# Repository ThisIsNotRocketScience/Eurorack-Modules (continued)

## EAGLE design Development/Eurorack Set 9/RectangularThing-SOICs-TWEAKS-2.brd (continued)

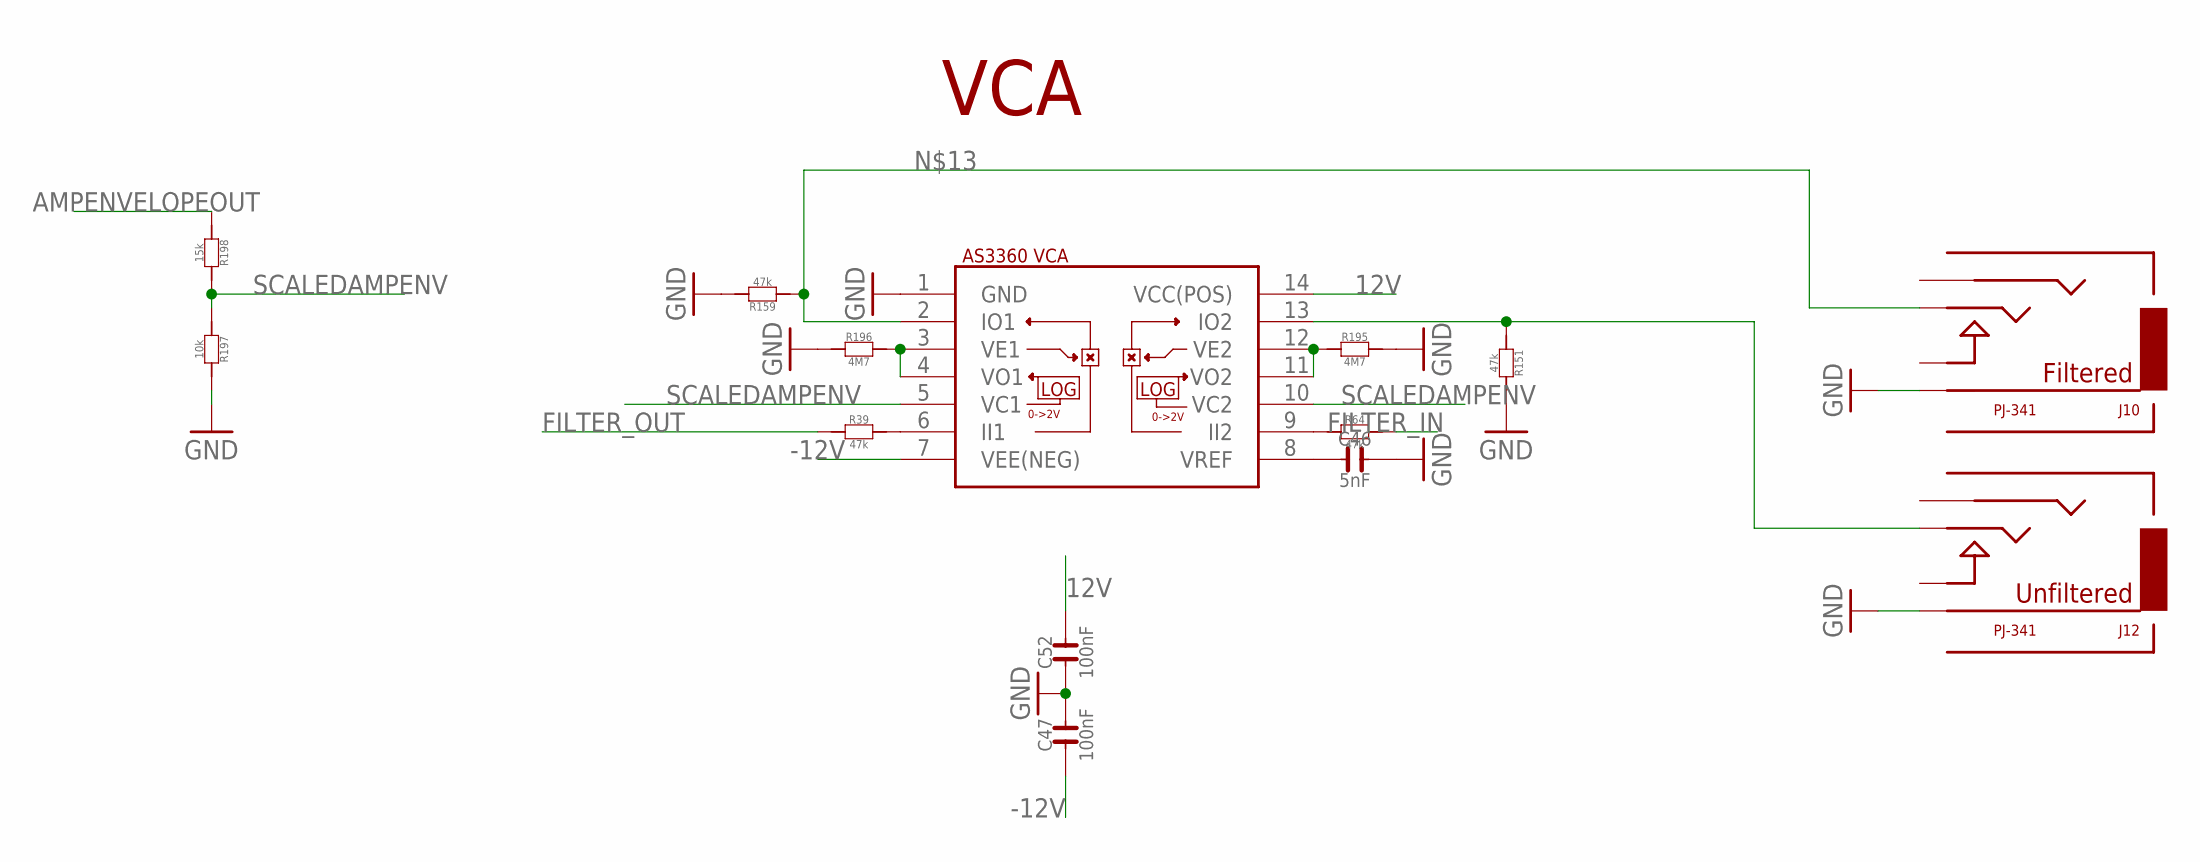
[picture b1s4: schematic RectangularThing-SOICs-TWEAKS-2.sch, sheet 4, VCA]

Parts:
C46: 5nF; C0603
C47, C52: 100nF; C0603
IC14: CEM3360SOIC14; SO14
J10, J12: PJ-341; 3.5MM-JACK-SWITCH-13MM-OUTPUT
R39, R64, R151, R159: 47k; R0603
R195, R196: 4M7; R0603
R197: 10k; R0603
R198: 15k; R0603

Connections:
12V: C52.2, IC14.14 (VCC(POS)); also elsewhere on the board
-12V: C47.1, IC14.7 (VEE(NEG)); also elsewhere on the board
AMPENVELOPEOUT: R198.1; also elsewhere on the board
FILTER_IN: R64.2; also elsewhere on the board
FILTER_OUT: R39.1; also elsewhere on the board
GND: C46.2, C47.2, C52.1, IC14.1 (GND), J10.RING@3 (RING), J12.RING@3 (RING), R151.2, R159.2, R195.2, R196.1, R197.2; also elsewhere on the board
unnamed: C46.1, IC14.8 (VREF)
unnamed: IC14.3 (VE1), IC14.4 (VO1), R196.2
unnamed: IC14.2 (IO1), J10.TIP@3 (TIP), R159.1
unnamed: IC14.13 (IO2), J12.TIP@3 (TIP), R151.1
unnamed: IC14.11 (VO2), IC14.12 (VE2), R195.1
unnamed: IC14.9 (II2), R64.1
unnamed: IC14.6 (II1), R39.2
SCALEDAMPENV: IC14.5 (VC1), IC14.10 (VC2), R197.1, R198.2

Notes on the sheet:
VCA

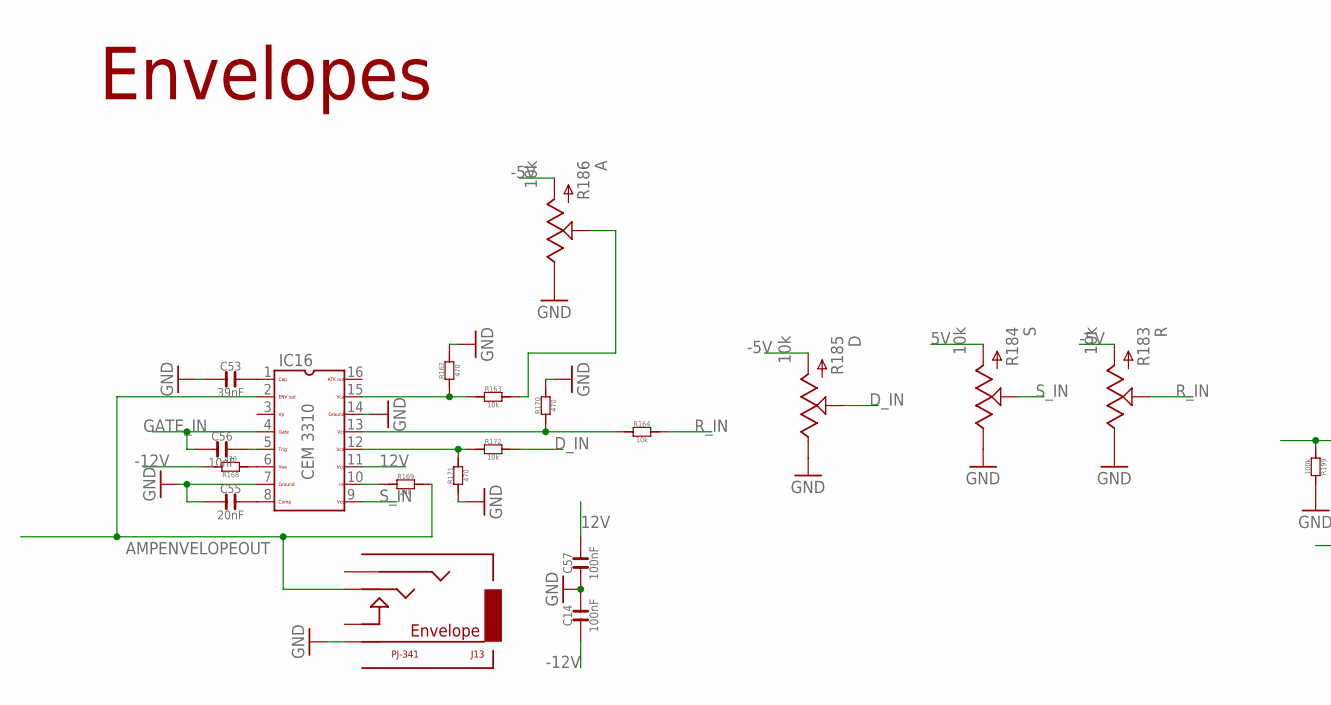
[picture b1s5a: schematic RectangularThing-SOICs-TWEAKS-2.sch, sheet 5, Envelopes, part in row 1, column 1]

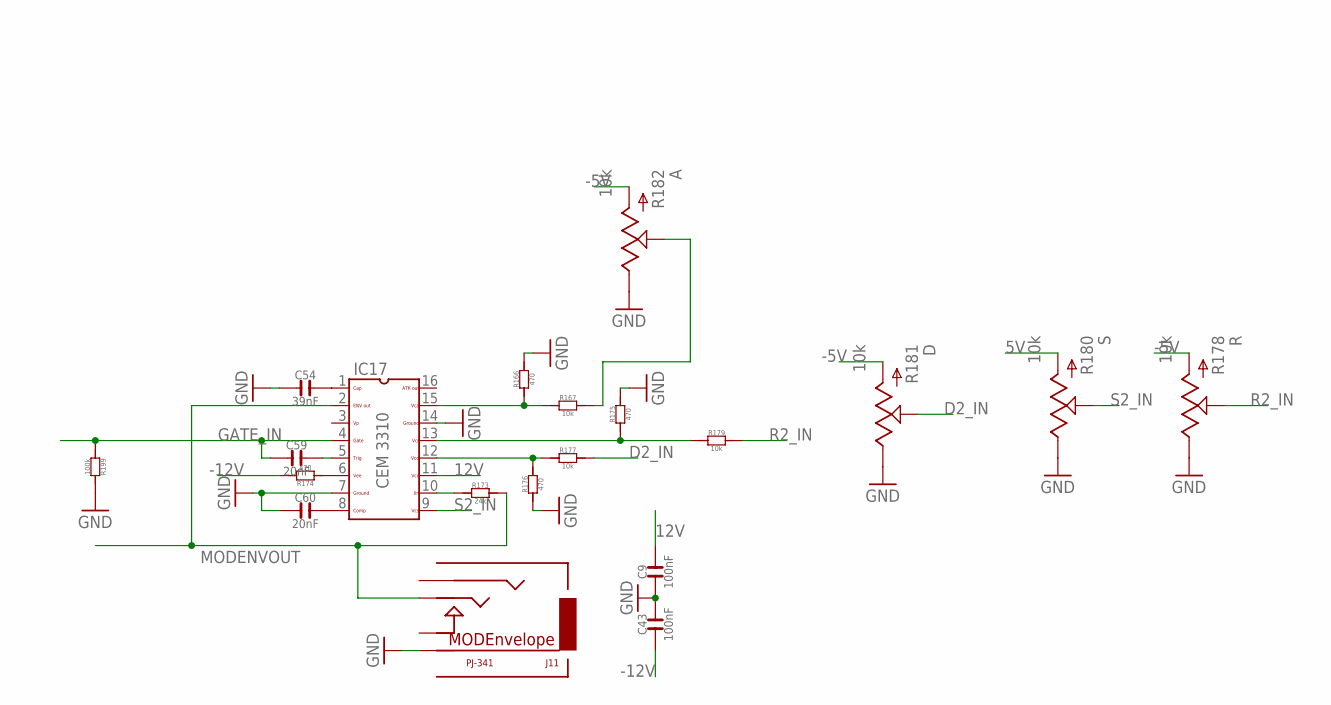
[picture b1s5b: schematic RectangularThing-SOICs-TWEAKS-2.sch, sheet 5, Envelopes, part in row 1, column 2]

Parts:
C9, C14, C43, C57: 100nF; C0603
C53, C54: 39nF; C0603
C55, C59, C60: 20nF; C0603
C56: 10nF; C0603
IC16, IC17: CEM3310SOIC16; SO16
J11, J13: PJ-341; 3.5MM-JACK-SWITCH-13MM-OUTPUT
R162, R166, R168, R170, R171, R174, R175, R176: 470; R0603
R163, R164, R167, R172, R177, R179: 10k; R0603
R169, R173: 24k; R0603
R178, R180, R181, R182, R183, R184, R185, R186: 10k; OG-POTS_ALPS_POT_VERTICAL
R199: 100k; R0603

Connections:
5V: R180.P$3 (A), R184.P$3 (A); also elsewhere on the board
12V: C9.2, C57.2, IC16.11, IC17.11; also elsewhere on the board
-5V: R178.P$3 (A), R181.P$3 (A), R182.P$3 (A), R183.P$3 (A), R185.P$3 (A), R186.P$3 (A); also elsewhere on the board
-12V: C14.1, C43.1, R168.2, R174.2; also elsewhere on the board
A2_IN: R167.2, R182.P$2 (S)
AMPENVELOPEOUT: IC16.2, J13.TIP@3 (TIP), R169.2; also elsewhere on the board
A_IN: R163.2, R186.P$2 (S)
D2_IN: R177.2, R181.P$2 (S)
D_IN: R172.2, R185.P$2 (S)
GATE_IN: C56.1, C59.1, IC16.4, IC17.4, R199.1; also elsewhere on the board
GND: C9.1, C14.2, C43.2, C53.1, C54.1, C55.1, C57.1, C60.1, IC16.7, IC16.14, IC17.7, IC17.14, J11.RING@3 (RING), J13.RING@3 (RING), R162.2, R166.2, R170.2, R171.1, R175.2, R176.1, R178.P$1 (E), R180.P$1 (E), R181.P$1 (E), R182.P$1 (E), R183.P$1 (E), R184.P$1 (E), R185.P$1 (E), R186.P$1 (E), R199.2; also elsewhere on the board
MODENVOUT: IC17.2, J11.TIP@3 (TIP), R173.2; also elsewhere on the board
unnamed: IC16.15, R162.1, R163.1
unnamed: IC16.12, R171.2, R172.1
unnamed: IC16.13, R164.1, R170.1
unnamed: C53.2, IC16.1
unnamed: C56.2, IC16.5
unnamed: IC16.6, R168.1
unnamed: C55.2, IC16.8
unnamed: IC16.10, R169.1
unnamed: IC17.15, R166.1, R167.1
unnamed: IC17.12, R176.2, R177.1
unnamed: IC17.13, R175.1, R179.1
unnamed: C59.2, IC17.5
unnamed: IC17.6, R174.1
unnamed: C60.2, IC17.8
unnamed: IC17.10, R173.1
unnamed: C54.2, IC17.1
R2_IN: R178.P$2 (S), R179.2
R_IN: R164.2, R183.P$2 (S)
S2_IN: IC17.9, R180.P$2 (S)
S_IN: IC16.9, R184.P$2 (S)

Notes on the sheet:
Envelopes

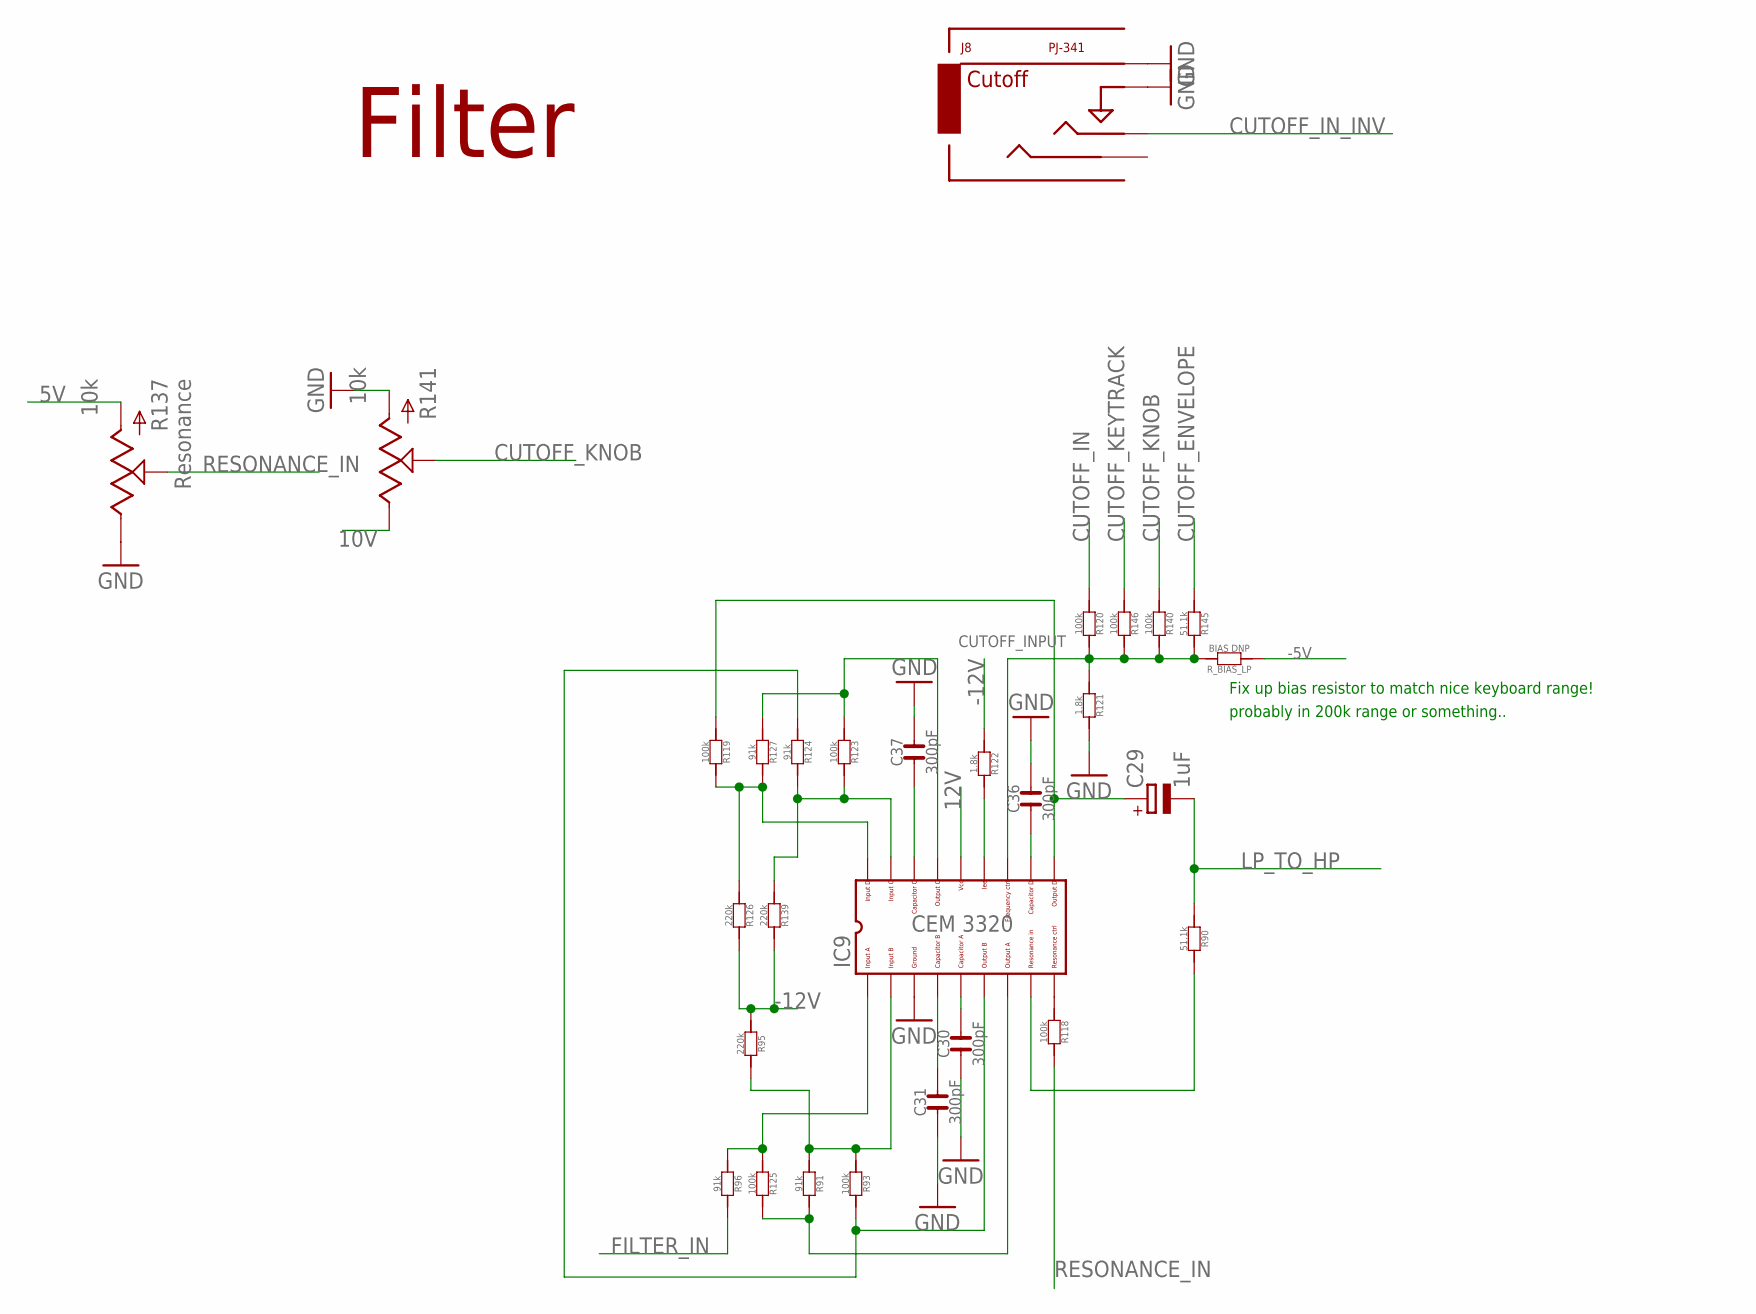
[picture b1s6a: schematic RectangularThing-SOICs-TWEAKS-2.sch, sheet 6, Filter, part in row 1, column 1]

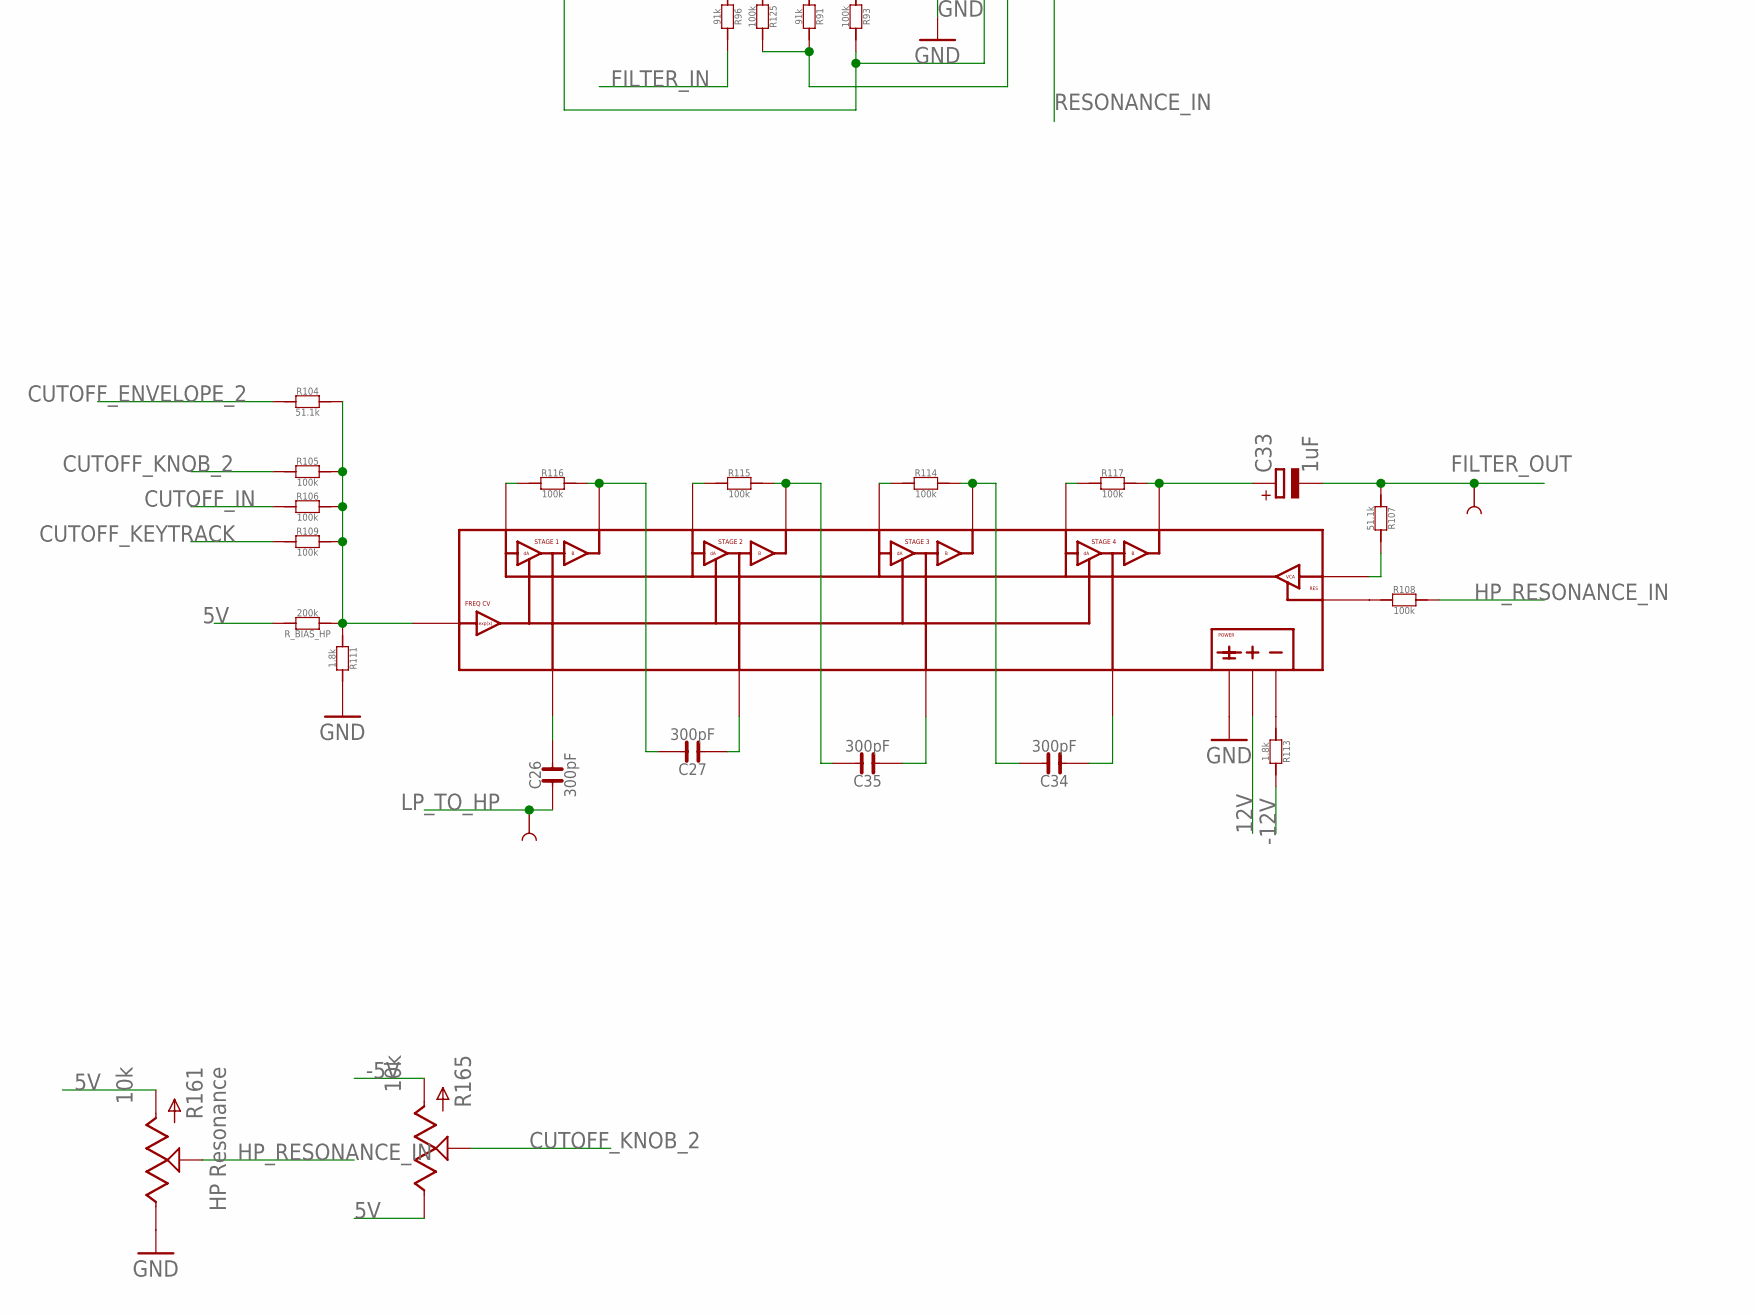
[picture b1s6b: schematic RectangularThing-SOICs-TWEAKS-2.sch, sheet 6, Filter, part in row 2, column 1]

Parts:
C26, C27, C30, C31, C34, C35, C36, C37: 300pF; C0603
C29, C33: 1uF; CASE_B
IC8: CEM3320_UNFOLDEDQFN; QFN24
IC9: CEM3320QFN24; QFN24
J8: PJ-341; 3.5MM-JACK-SWITCH-13MM-INPUT
R90, R104, R107, R145: 51.1k; R0603
R91, R96, R124, R127: 91k; R0603
R93, R105, R106, R108, R109, R114, R115, R116, R117, R118, R119, R120, R123, R125, R140, R146: 100k; R0603
R95, R126, R139: 220k; R0603
R111, R113, R121, R122: 1.8k; R0603
R137, R161: 10k; OG-POTS_ALPS_POT_VERTICAL
R141, R165: 10k; OG-POTS_ALPS_POT_VERTICAL_WITHBIGKNOB
R_BIAS_HP: 200k; R0603
R_BIAS_LP: BIAS DNP; R0603
TP7, TP8: TEST-POINT3X5; PAD.03X.05

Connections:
5V: R137.P$3 (A), R161.P$3 (A), R165.P$1 (E), R_BIAS_HP.2; also elsewhere on the board
10V: R141.P$1 (E); also elsewhere on the board
12V: IC8.P$22 (POSRAIL), IC9.P$22 (14); also elsewhere on the board
-5V: R165.P$3 (A), R_BIAS_LP.1; also elsewhere on the board
-12V: R95.1, R113.2, R122.1, R126.2, R139.2; also elsewhere on the board
CUTOFF_ENVELOPE: R145.1; also elsewhere on the board
CUTOFF_ENVELOPE_2: R104.1; also elsewhere on the board
CUTOFF_IN: R106.1, R120.1; also elsewhere on the board
CUTOFF_INPUT: IC9.P$19 (12), R120.2, R121.1, R140.2, R145.2, R146.2, R_BIAS_LP.2
CUTOFF_IN_INV: J8.TIP@3 (TIP); also elsewhere on the board
CUTOFF_KEYTRACK: R109.1, R146.1; also elsewhere on the board
CUTOFF_KNOB: R140.1, R141.P$2 (S)
CUTOFF_KNOB_2: R105.1, R165.P$2 (S)
FILTER_IN: R96.2; also elsewhere on the board
FILTER_OUT: C33.-, R107.1, TP7.P$1; also elsewhere on the board
GND: C30.1, C31.1, C36.2, C37.2, IC8.P$7 (GROUND), IC9.P$7 (3), J8.RING@3 (RING), J8.SWITCH@3 (SWITCH), R111.2, R121.2, R137.P$1 (E), R141.P$3 (A), R161.P$1 (E); also elsewhere on the board
HP_FILTER_CUTOFF_IN: IC8.P$19 (FREQCV), R104.2, R105.2, R106.2, R109.2, R111.1, R_BIAS_HP.1
HP_RESONANCE_IN: R108.2, R161.P$2 (S)
LP_TO_HP: C26.1, C29.-, R90.1, TP8.P$1
unnamed: C37.1, IC9.P$24 (16)
unnamed: C31.2, IC9.P$8 (4)
unnamed: C30.2, IC9.P$9 (5)
unnamed: C36.1, IC9.P$17 (11)
unnamed: IC9.P$15 (9), R118.1
unnamed: IC9.P$4 (1), R96.1, R125.1
unnamed: IC9.P$12 (7), R91.2, R125.2
unnamed: IC9.P$11 (6), R93.2, R124.1
unnamed: IC9.P$3 (18), R119.2, R126.1, R127.2
unnamed: IC9.P$2 (17), R123.2, R124.2, R139.1
unnamed: IC9.P$23 (15), R123.1, R127.1
unnamed: IC9.P$20 (13), R122.2
unnamed: C29.+, IC9.P$16 (10), R119.1
unnamed: IC9.P$14 (8), R90.2
unnamed: IC9.P$5 (2), R91.1, R93.1, R95.2
unnamed: IC8.P$20 (NEGRAIL), R113.1
unnamed: IC8.P$15 (RESONANCE_CV), R108.1
unnamed: C26.2, IC8.P$9 (STAGE1_CAP)
unnamed: IC8.P$4 (STAGE1_IN), R116.1
unnamed: C27.2, IC8.P$12 (STAGE1_OUT), R116.2
unnamed: C27.1, IC8.P$8 (STAGE2_CAP)
unnamed: IC8.P$5 (STAGE2_IN), R115.1
unnamed: C35.2, IC8.P$11 (STAGE2_OUT), R115.2
unnamed: C35.1, IC8.P$24 (STAGE3_CAP)
unnamed: IC8.P$2 (STAGE3_IN), R114.1
unnamed: C34.2, IC8.P$23 (STAGE3_OUT), R114.2
unnamed: C34.1, IC8.P$17 (STAGE4_CAP)
unnamed: IC8.P$3 (STAGE4_IN), R117.1
unnamed: C33.+, IC8.P$16 (STAGE4_OUT), R117.2
unnamed: IC8.P$14 (FEEDBACK_IN), R107.2
RESONANCE_IN: R118.2, R137.P$2 (S)

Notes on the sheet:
Filter
Fix up bias resistor to match nice keyboard range!
probably in 200k range or something..

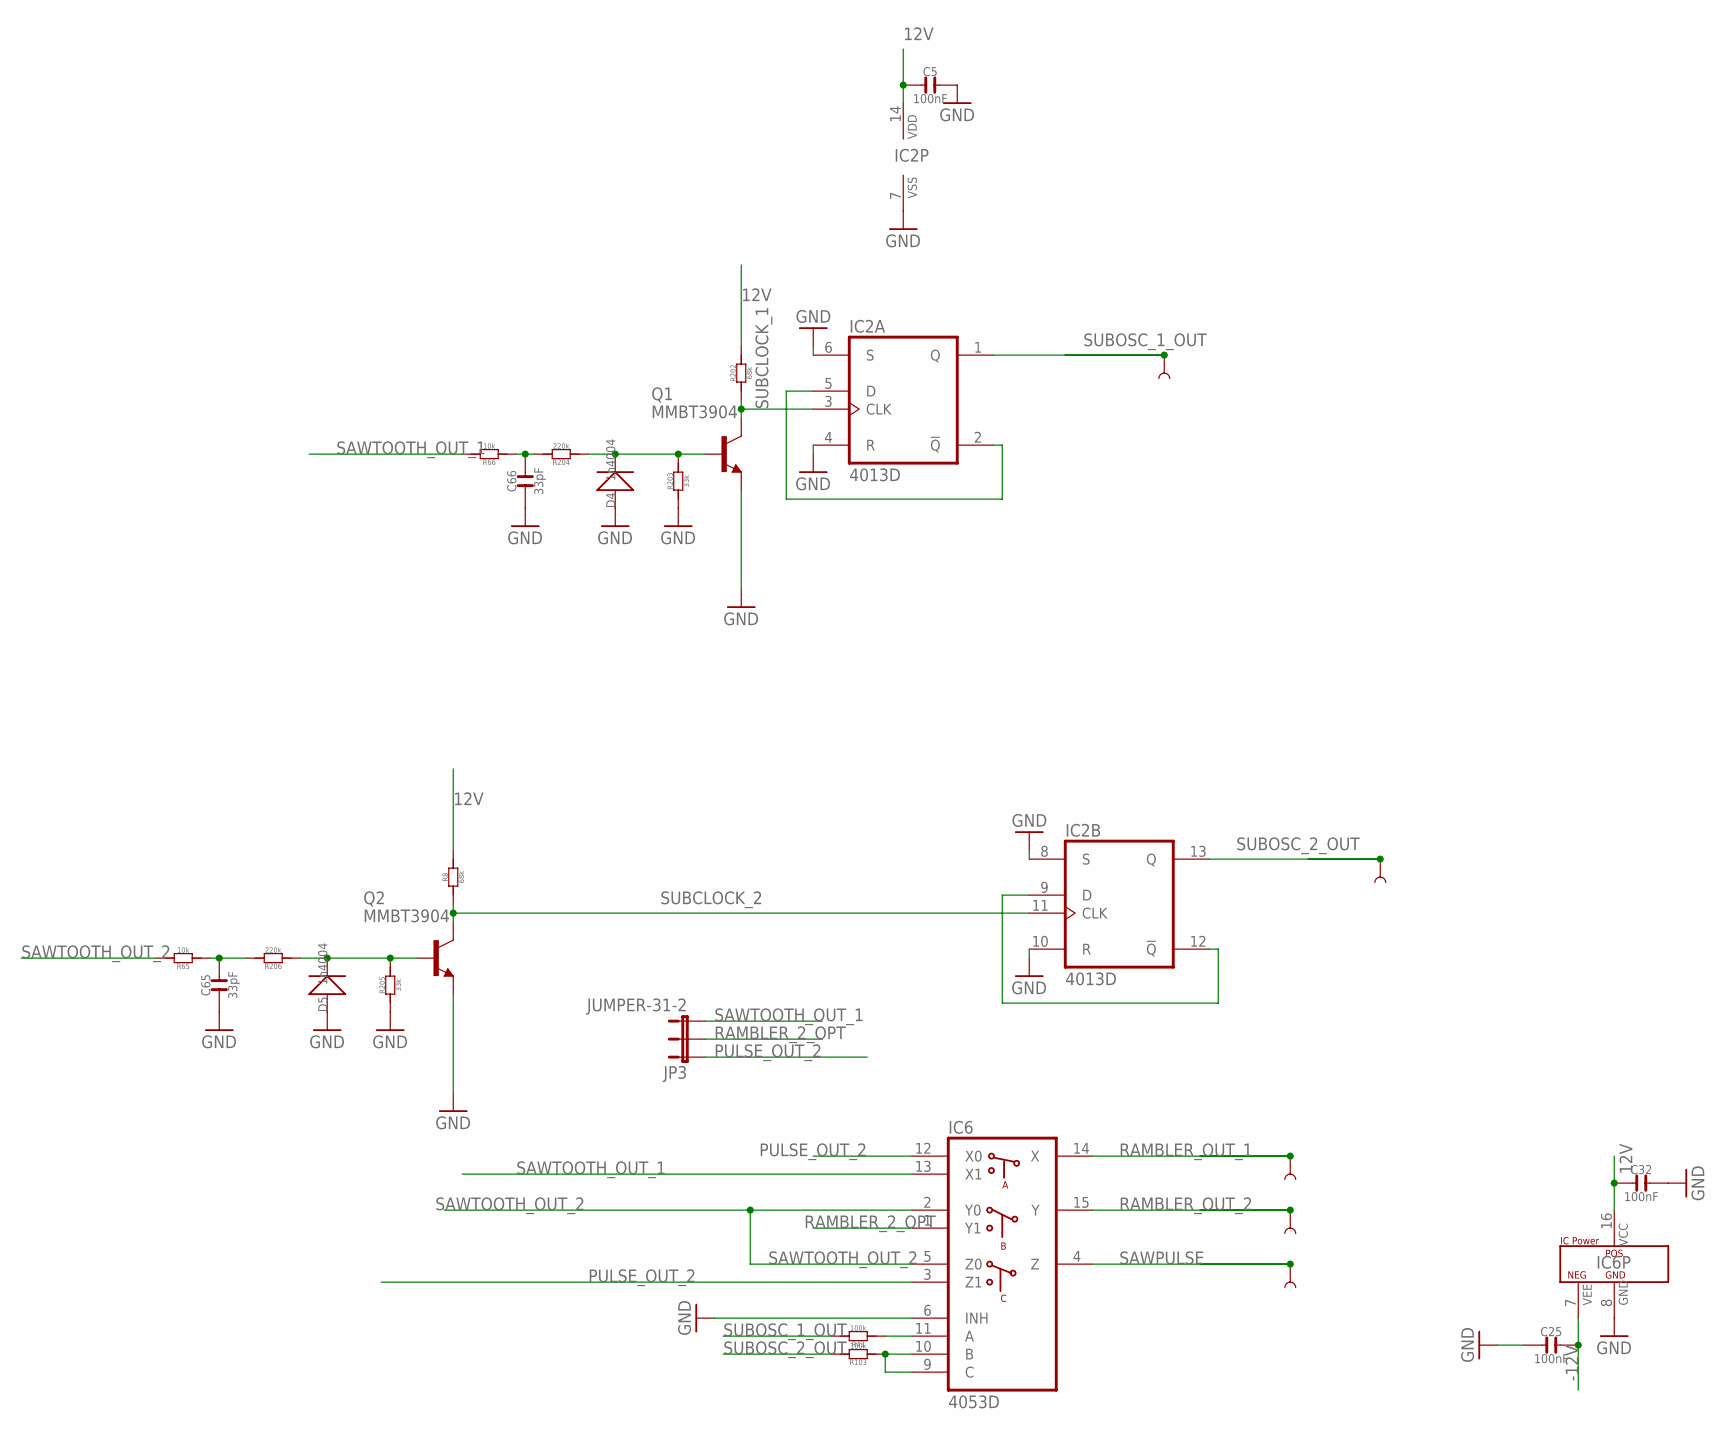
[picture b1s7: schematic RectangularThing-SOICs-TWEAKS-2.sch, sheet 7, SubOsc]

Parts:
C5, C25, C32: 100nF; C0603
C65, C66: 33pF; C0603
D4, D5: 1n4004; DO-214AC
IC2: 4013D; SO14
IC6: 4053D; SO16
JP3: JUMPER-31-2; SJ_3_PASTE1&2
Q1, Q2: MMBT3904; SOT23-BEC; MPN PMBT3904,215
R8, R202: 68k; R0603
R43, R103: 100k; R0603
R65, R66: 10k; R0603
R203, R205: 33k; R0603
R204, R206: 220k; R0603
TP1, TP2, TP4, TP5, TP6: TEST-POINT3X5; PAD.03X.05

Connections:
12V: C5.1, C32.1, IC2.14 (VDD), IC6.16 (VCC), R8.2, R202.2; also elsewhere on the board
-12V: C25.2, IC6.7 (VEE); also elsewhere on the board
GND: C5.2, C25.1, C32.2, C65.1, C66.1, D4.1 (+), D5.1 (+), IC2.4 (R), IC2.6 (S), IC2.7 (VSS), IC2.8 (S), IC2.10 (R), IC6.6 (INH), IC6.8 (GND), Q1.E, Q2.E, R203.1, R205.1; also elsewhere on the board
unnamed: IC6.9 (C), IC6.10 (B), R103.1
unnamed: D5.2 (-), Q2.B, R205.2, R206.1
unnamed: C65.2, R65.1, R206.2
unnamed: IC6.11 (A), R43.1
unnamed: C66.2, R66.1, R204.2
unnamed: D4.2 (-), Q1.B, R203.2, R204.1
PULSE_OUT_2: IC6.3 (Z1), IC6.12 (X0), JP3.1; also elsewhere on the board
RAMBLER_2_OPT: IC6.1 (Y1), JP3.2
RAMBLER_OUT_1: IC6.14 (X), TP5.P$1; also elsewhere on the board
RAMBLER_OUT_2: IC6.15 (Y), TP4.P$1; also elsewhere on the board
SAWPULSE: IC6.4 (Z), TP6.P$1; also elsewhere on the board
SAWTOOTH_OUT_1: IC6.13 (X1), JP3.3, R66.2; also elsewhere on the board
SAWTOOTH_OUT_2: IC6.2 (Y0), IC6.5 (Z0), R65.2; also elsewhere on the board
SUBCLOCK_1: IC2.3 (CLK), Q1.C, R202.1
SUBCLOCK_2: IC2.11 (CLK), Q2.C, R8.1
SUBOSC1_FEEDBACK: IC2.2 (!Q), IC2.5 (D)
SUBOSC2_FEEDBACK: IC2.9 (D), IC2.12 (!Q)
SUBOSC_1_OUT: IC2.1 (Q), R43.2, TP2.P$1; also elsewhere on the board
SUBOSC_2_OUT: IC2.13 (Q), R103.2, TP1.P$1; also elsewhere on the board

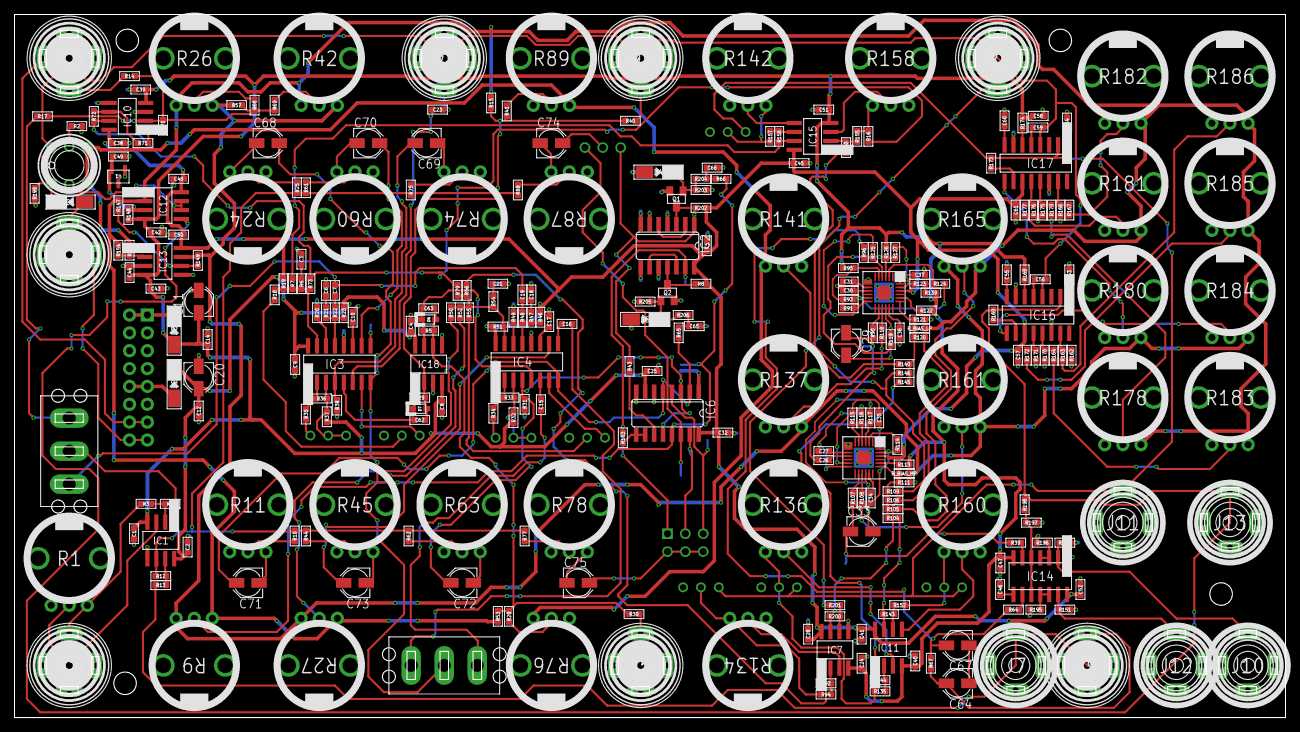
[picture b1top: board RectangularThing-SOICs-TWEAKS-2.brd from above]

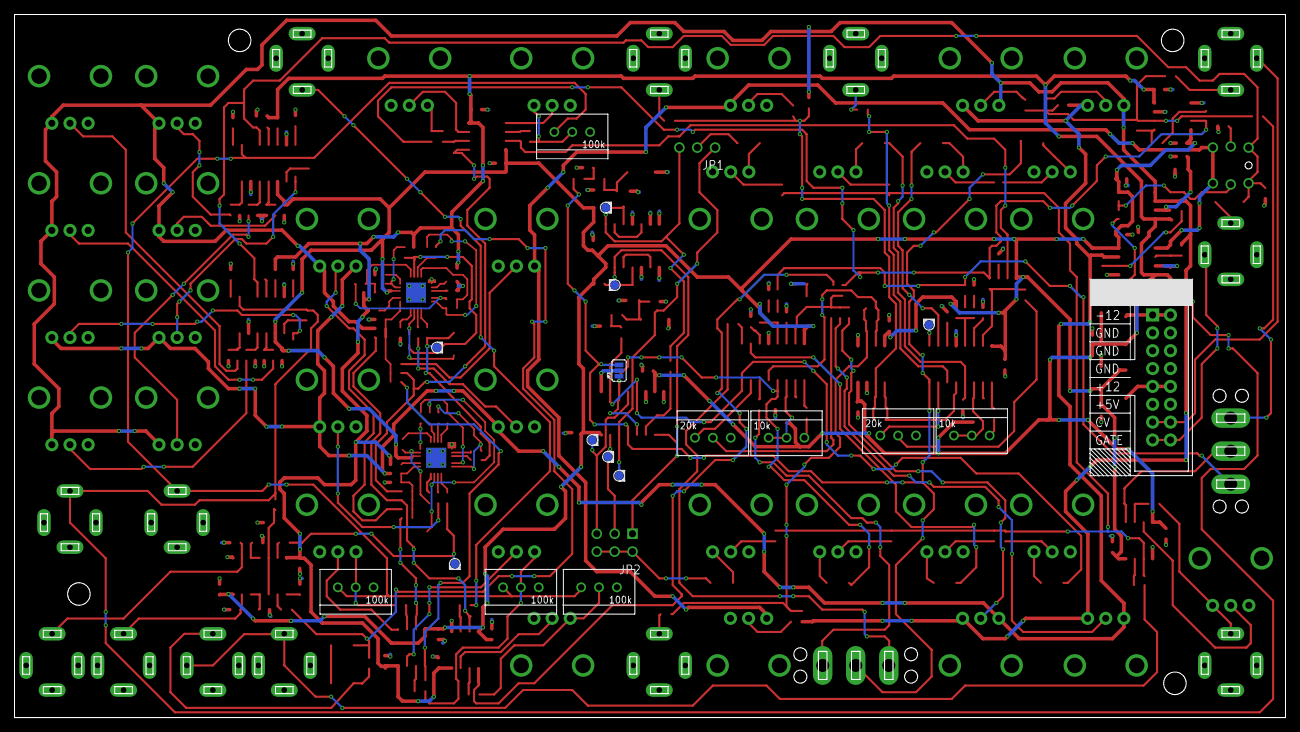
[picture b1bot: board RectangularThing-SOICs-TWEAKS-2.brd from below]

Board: 2 copper layers, 180.8 x 100.0 mm, 317 parts (20 on the bottom side), 214 nets.

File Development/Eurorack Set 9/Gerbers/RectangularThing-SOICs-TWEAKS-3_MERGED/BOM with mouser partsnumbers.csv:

Qty,Mouser,Place,Value,Device,Package,Parts
1,755-SFR03EZPJ000,yes,0,R-0603,R0603,R67
2,603-AC0603FR-071M5L,yes,1.5M,R-0603,R0603,"R23, R46"
6,603-AC0603FR-071K8L,yes,1.8k,R-0603,R0603,"R20, R49, R111, R113, R121, R122"
4,756-GWCR0603-100RFT5,yes,100,R-0603,R0603,"R13, R16, R84, R85"
64,603-AC0603FR-07100KL,yes,100k,R-0603,R0603,"R3, R4, R5, R7, R10, R12, R14, R15, R17, R25, R29, R30, R40, R43, R50, R53, R56, R57, R58, R59, R69, R70, R71, R72, R77, R80, R81, R82, R83, R88, R92, R93, R94, R103, R105, R106, R108, R109, R114, R115, R116, R117, R118, R119, R120, R123, R125, R135, R140, R143, R144, R146, R147, R149, R150, R152, R154, R155, R156, R157, R199, R200, R201, R_BIAS_HP"
4,,no,100k,TRIMPOT,TRIMPOT,"R191, R192, R193, R194"
2,667-ERJ-PB3B1003V,yes,100k 0.1%,R-0603,R0603,"R73, R79"
39,710-885012206095,yes,100nF,C-0603,C0603,"C1, C2, C4, C5, C7, C8, C9, C12, C13, C14, C19, C22, C24, C25, C28, C32, C38, C39, C40, C41, C42, C43, C44, C45, C47, C48, C49, C50, C51, C52, C57, C58, C61, C76, C77, C78, C79, C80, C81"
24,,no,10k,POTSQUAREHOLE_SMALLKNOB,ALPS_POT_SQUAREHOLES,"R1, R9, R26, R27, R42, R76, R89, R134, R136, R137, R141, R142, R158, R160, R161, R165, R178, R180, R181, R182, R183, R184, R185, R186"
12,603-AC0603FR-0710KL,yes,10k,R-0603,R0603,"R62, R65, R66, R75, R148, R163, R164, R167, R172, R177, R179, R197"
2,,no,10k,TRIMPOT,TRIMPOT,"R187, R190"
8,,no,10kA,POTSQUAREHOLE_SMALLKNOB,ALPS_POT_SQUAREHOLES,"R11, R24, R45, R60, R63, R74, R78, R87"
7,80-C0603X103K1RT500,yes,10nF,C-0603,C0603,"C3, C6, C18, C21, C56, C62, C63"
12,710-865230440002,yes,10u,CAPACITOR_POL-CASE_B,CASE_B,"C11, C20, C64, C67, C68, C69, C70, C71, C72, C73, C74, C75"
1,603-AC0603FR-0715KL,yes,15k,R-0603,R0603,R198
6,603-AC0603FR-071ML,yes,1M,R-0603,R0603,"R18, R22, R48, R52, R55, R68"
1,603-AC0603FR-071KL,yes,1k,R-0603,R0603,R2
2,750-CGRA4004-G,yes,1n4004,D-SMA,DO-214AC,"D2, D3"
5,80-C0603C102J5G,yes,1nF C0G,C-0603,C0603,"C10, C15, C16, C17, C23"
2,710-865230640005,yes,1uF,CAPACITOR_POL-CASE_B,CASE_B,"C29, C33"
2,,no,1x3pin header,M031X03_NO_SILK,1X03_NO_SILK,"JP1, JP5"
3,603-AC0603FR-07200KL,yes,200k,R-0603,R0603,"R28, R41, R153"
2,,no,20k,TRIMPOT,TRIMPOT,"R188, R189"
3,80-C0603C223J3R,yes,20nF,C-0603,C0603,"C55, C59, C60"
5,603-AC0603FR-07220KL,yes,220k,R-0603,R0603,"R95, R126, R139, R204, R206"
4,603-AC0603FR-0724KL,yes,24k,R-0603,R0603,"R34, R35, R169, R173"
2,,no,2x3pin header,M03X2NO_SILK,2X3-NS,"JP2, JP4"
8,81-GRM185C1H301JA01D,yes,300pF,C-0603,C0603,"C26, C27, C30, C31, C34, C35, C36, C37"
2,603-AC0603FR-0733KL,yes,33k,R-0603,R0603,"R203, R205"
2,80-C0603C330J5GAUTO,yes,33pF,C-0603,C0603,"C65, C66"
2,603-AC0603FR-07360KL,yes,360k,R-0603,R0603,"R19, R51"
2,80-C0603C393J4R,yes,39nF,C-0603,C0603,"C53, C54"
1,595-CD4013BM96G4,yes,4013D,4013D,SO14,IC2
1,700-MAX4053CSE,yes,4053D,4053D,SO16,IC6
12,603-AC0603FR-07470RL,yes,470,R-0603,R0603,"R6, R21, R47, R54, R162, R166, R168, R170, R171, R174, R175, R176"
4,603-AC0603FR-0747KL,yes,47k,R-0603,R0603,"R39, R64, R151, R159"
2,603-AC0603FR-074M7L,yes,4M7,R-0603,R0603,"R195, R196"
2,603-AC0603FR-075K6L,yes,5.6k,R-0603,R0603,"R33, R36"
10,603-AC0603FR-0751K1L,yes,51.1k,R-0603,R0603,"R90, R104, R107, R145, R31, R32, R37, R38, R44, R61"
1,80-C0603C473J4R,yes,5nF,C-0603,C0603,C46
2,603-AC0603FR-0768KL,yes,68k,R-0603,R0603,"R8, R202"
4,603-AC0603FR-0791KL,yes,91k,R-0603,R0603,"R91, R96, R124, R127"
5,726-BAS16WH6327,yes,BAS16W,BAS16W,SOT-323,"D4, D5, D6, D8, D9"
1,,no,BIAS DNP,R-0603,R0603,R_BIAS_LP
2,not on mouser - AlfaRP ,yes,CEM3310SOIC16,CEM3310SOIC16,SO16,"IC16, IC17"
2,not on mouser - AlfaRP ,yes,CEM3320QFN24,CEM3320QFN24,QFN24,"IC8, IC9"
2,not on mouser - AlfaRP ,yes,CEM3340SOIC16,CEM3340SOIC16,SO16,"IC3, IC4"
1,not on mouser - AlfaRP ,yes,CEM3360SOIC14,CEM3360SOIC14,SO14,IC14
1,,no,EURORACK_PCB36HP_10CM,EURORACK_PCB36HP_10CM,EURORACK36HP,PCB1
1,700-LM4040DIM3-5.0T,yes,LM4040DIM3-5.0,LM4040DIM3-5.0,SOT95P237X112-3N,U1
2,771-MMBT3904T/R,yes,MMBT3904,MMBT3904LT1-NPN-SOT23-BEC,SOT23-BEC,"Q1, Q2"
4,,no,MOUNT-HOLE,MOUNT-HOLE,3.2-NOMARKINGS-SMALLSAFEZONE,"H1, H2, H3, H4"
2,,no,ONOFFON,ONOFFON,MULTICOMP1MS-ONOFFON,"S1, S3"
10,,no,PJ-341,AUDIO-JACKINPUT,3.5MM-JACK-SWITCH-13MM-INPUT,"J1, J2, J3, J4, J5, J6, J8, J9, J15, J16"
5,,no,PJ-341,AUDIO-JACKOUTPUT,3.5MM-JACK-SWITCH-13MM-OUTPUT,"J7, J10, J11, J12, J13"
1,,no,POWERSHROUDED,POWERSHROUDED,POWER_16_SHROUDED,J14
1,,no,SWITCH_W_LED_PB6149L-X-102YELLOW,SWITCH_W_LED_PB6149L-X-102YELLOW,PB6149L,S2
1,,no,TEST-POINT3X5,TEST-POINT3X5,PAD.03X.05,TP3
12,595-TL072CDR,yes,TL072,TL072,SO08,"IC1, IC5, IC7, IC10, IC11, IC12, IC13, IC15, IC18, IC19, IC20, IC21"
